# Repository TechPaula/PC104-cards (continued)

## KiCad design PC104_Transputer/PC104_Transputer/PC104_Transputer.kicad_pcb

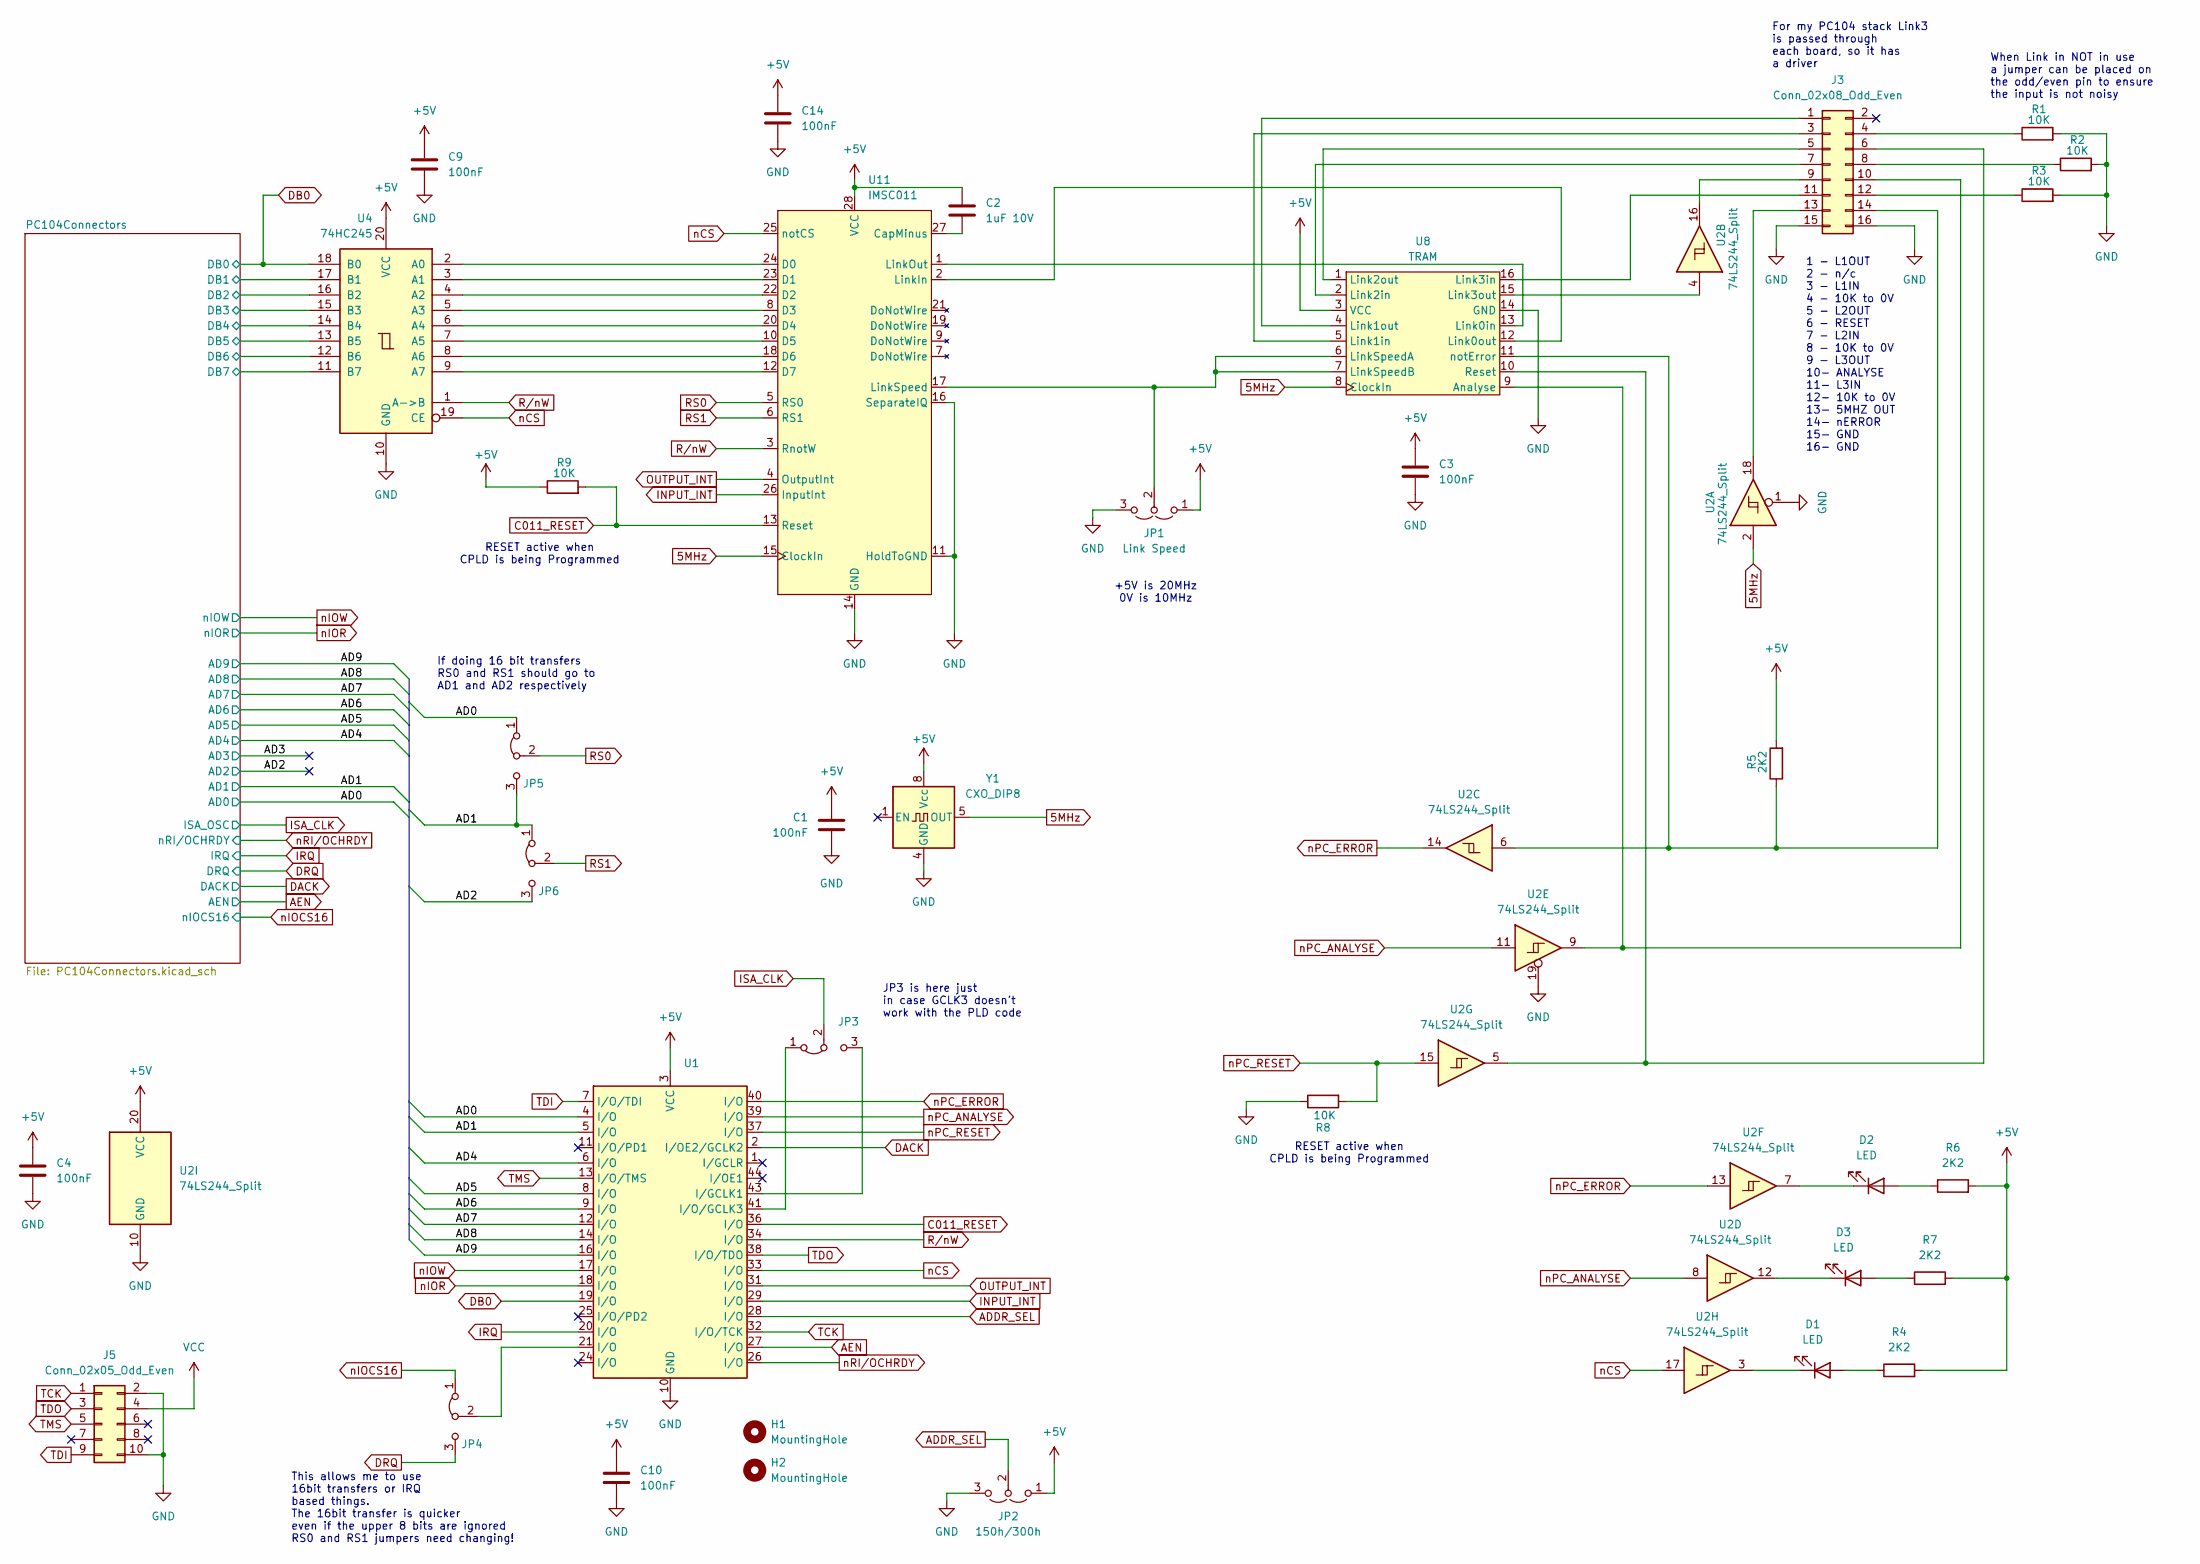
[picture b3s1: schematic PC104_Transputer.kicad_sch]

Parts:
C1, C3, C4, C9, C10, C14: 100nF; C_0805_2012Metric
C2: 1uF 10V; C_0805_2012Metric
D1, D2, D3: LED; LED_0603_1608Metric
H1, H2: MountingHole; MountingHole_2.5mm
J3: Conn_02x08_Odd_Even; PinHeader_2x08_P2.54mm_Horizontal
J5: Conn_02x05_Odd_Even; PinHeader_2x05_P2.54mm_Vertical
JP1: Link Speed; PinHeader_1x03_P2.54mm_Vertical
JP2: 150h/300h; PinHeader_1x03_P2.54mm_Vertical
JP3, JP4, JP5, JP6: Jumper_3_Bridged12; SolderJumper-3_P1.3mm_Bridged12_RoundedPad1.0x1.5mm_NumberL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
R1, R2, R3, R8, R9: 10K; R_0402_1005Metric
R4, R6, R7: 2K2; R_0603_1608Metric
R5: 2K2; R_0402_1005Metric
U1: PLCC-44_THT-Socket
U2: 74LS244_Split; SOIC-20W_7.5x12.8mm_P1.27mm
U4: 74HC245; SOIC-20W_7.5x12.8mm_P1.27mm
U8: TRAM
U11: IMSC011; DIP-28_W15.24mm
Y1: CXO_DIP8; Oscillator_DIP-8

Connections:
5MHz: U2.2, U8.8 (ClockIn), U11.15 (ClockIn), Y1.5 (OUT)
+5V: C1.1, C2.1, C3.1, C4.1, C9.1, C10.1, C14.1, JP1.1 (A), JP2.1 (A), R4.2, R5.2, R6.2, R7.2, R9.1, U1.3 (VCC), U1.15 (VCC), U1.23 (VCC), U1.35 (VCC), U2.20 (VCC), U4.20 (VCC), U8.3 (VCC), U11.28 (VCC), Y1.8 (Vcc); also elsewhere on the board
/AD0: JP5.1 (A), U1.4 (I/O); also elsewhere on the board
/AD1: JP5.3 (B), JP6.1 (A), U1.5 (I/O); also elsewhere on the board
/AD2: JP6.3 (B); also elsewhere on the board
/AD4: U1.6 (I/O); also elsewhere on the board
/AD5: U1.8 (I/O); also elsewhere on the board
/AD6: U1.9 (I/O); also elsewhere on the board
/AD7: U1.12 (I/O); also elsewhere on the board
/AD8: U1.14 (I/O); also elsewhere on the board
/AD9: U1.16 (I/O); also elsewhere on the board
/PC104Connectors/DB1: U4.17 (B1); also elsewhere on the board
/PC104Connectors/DB2: U4.16 (B2); also elsewhere on the board
/PC104Connectors/DB3: U4.15 (B3); also elsewhere on the board
/PC104Connectors/DB4: U4.14 (B4); also elsewhere on the board
/PC104Connectors/DB5: U4.13 (B5); also elsewhere on the board
/PC104Connectors/DB6: U4.12 (B6); also elsewhere on the board
/PC104Connectors/DB7: U4.11 (B7); also elsewhere on the board
ADDR_SEL: JP2.2 (C), U1.28 (I/O)
AEN: U1.27 (I/O); also elsewhere on the board
C011_RESET: R9.2, U1.36 (I/O), U11.13 (Reset)
DACK: U1.2 (I/OE2/GCLK2); also elsewhere on the board
DB0: U1.19 (I/O), U4.18 (B0); also elsewhere on the board
DRQ: JP4.3 (B); also elsewhere on the board
GND: C1.2, C3.2, C4.2, C9.2, C10.2, C14.2, J3.15, J3.16, J5.2, J5.10, JP1.3 (B), JP2.3 (B), R1.2, R2.2, R3.2, R8.1, U1.10 (GND), U1.22 (GND), U1.30 (GND), U1.42 (GND), U2.1, U2.10 (GND), U2.19, U4.10 (GND), U8.14 (GND), U11.11 (HoldToGND), U11.14 (GND), U11.16 (SeparateIQ), Y1.4 (GND); also elsewhere on the board
INPUT_INT: U1.29 (I/O), U11.26 (InputInt)
IRQ: U1.20 (I/O); also elsewhere on the board
ISA_CLK: JP3.2 (C); also elsewhere on the board
unnamed: D1.2 (A), R4.1
unnamed: D1.1 (K), U2.3
unnamed: D2.2 (A), R6.1
unnamed: D2.1 (K), U2.7
unnamed: D3.2 (A), R7.1
unnamed: D3.1 (K), U2.12
unnamed: J3.1, U8.4 (Link1out)
unnamed: J3.3, U8.5 (Link1in)
unnamed: J3.4, R1.1
unnamed: J3.5, U8.1 (Link2out)
unnamed: J3.6, U2.5, U8.10 (Reset)
unnamed: J3.7, U8.2 (Link2in)
unnamed: J3.8, R2.1
unnamed: J3.9, U2.16
unnamed: J3.10, U2.9, U8.9 (Analyse)
unnamed: J3.11, U8.16 (Link3in)
unnamed: J3.12, R3.1
unnamed: J3.13, U2.18
unnamed: J3.14, R5.1, U2.6, U8.11 (notError)
unnamed: JP1.2 (C), U8.6 (LinkSpeedA), U8.7 (LinkSpeedB), U11.17 (LinkSpeed)
unnamed: JP3.1 (A), U1.41 (I/O/GCLK3)
unnamed: JP3.3 (B), U1.43 (I/GCLK1)
unnamed: JP4.2 (C), U1.21 (I/O)
unnamed: U2.4, U8.15 (Link3out)
unnamed: C2.2, U11.27 (CapMinus)
unnamed: U4.2 (A0), U11.24 (D0)
unnamed: U4.3 (A1), U11.23 (D1)
unnamed: U4.4 (A2), U11.22 (D2)
unnamed: U4.5 (A3), U11.8 (D3)
unnamed: U4.6 (A4), U11.20 (D4)
unnamed: U4.7 (A5), U11.10 (D5)
unnamed: U4.8 (A6), U11.18 (D6)
unnamed: U4.9 (A7), U11.12 (D7)
unnamed: U8.12 (Link0out), U11.2 (LinkIn)
unnamed: U8.13 (Link0in), U11.1 (LinkOut)
OUTPUT_INT: U1.31 (I/O), U11.4 (OutputInt)
RS0: JP5.2 (C), U11.5 (RS0)
RS1: JP6.2 (C), U11.6 (RS1)
R/nW: U1.34 (I/O), U4.1 (A->B), U11.3 (RnotW)
TCK: J5.1, U1.32 (I/O/TCK)
TDI: J5.9, U1.7 (I/O/TDI)
TDO: J5.3, U1.38 (I/O/TDO)
TMS: J5.5, U1.13 (I/O/TMS)
VCC: J5.4
nCS: U1.33 (I/O), U2.17, U4.19 (CE), U11.25 (notCS)
nIOCS16: JP4.1 (A); also elsewhere on the board
nIOR: U1.18 (I/O); also elsewhere on the board
nIOW: U1.17 (I/O); also elsewhere on the board
nPC_ANALYSE: U1.39 (I/O), U2.8, U2.11
nPC_ERROR: U1.40 (I/O), U2.13, U2.14
nPC_RESET: R8.2, U1.37 (I/O), U2.15
nRI/OCHRDY: U1.26 (I/O); also elsewhere on the board

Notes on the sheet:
When Link in NOT in use a jumper can be placed on the odd/even pin to ensure the input is not noisy
RESET active when CPLD is being Programmed
JP3 is here just in case GCLK3 doesn't work with the PLD code
For my PC104 stack Link3 is passed through each board, so it has a driver
If doing 16 bit transfers RS0 and RS1 should go to AD1 and AD2 respectively
This allows me to use 16bit transfers or IRQ based things. The 16bit transfer is quicker even if the upper 8 bits are ignored RS0 and RS1 jumpers need changing!
1 - L1OUT 2 - n/c 3 - L1IN 4 - 10K to 0V 5 - L2OUT 6 - RESET 7 - L2IN 8 - 10K to 0V 9 - L3OUT 10- ANALYSE 11- L3IN 12- 10K to 0V 13- 5MHZ OUT 14- nERROR 15- GND 16- GND
+5V is 20MHz 0V is 10MHz

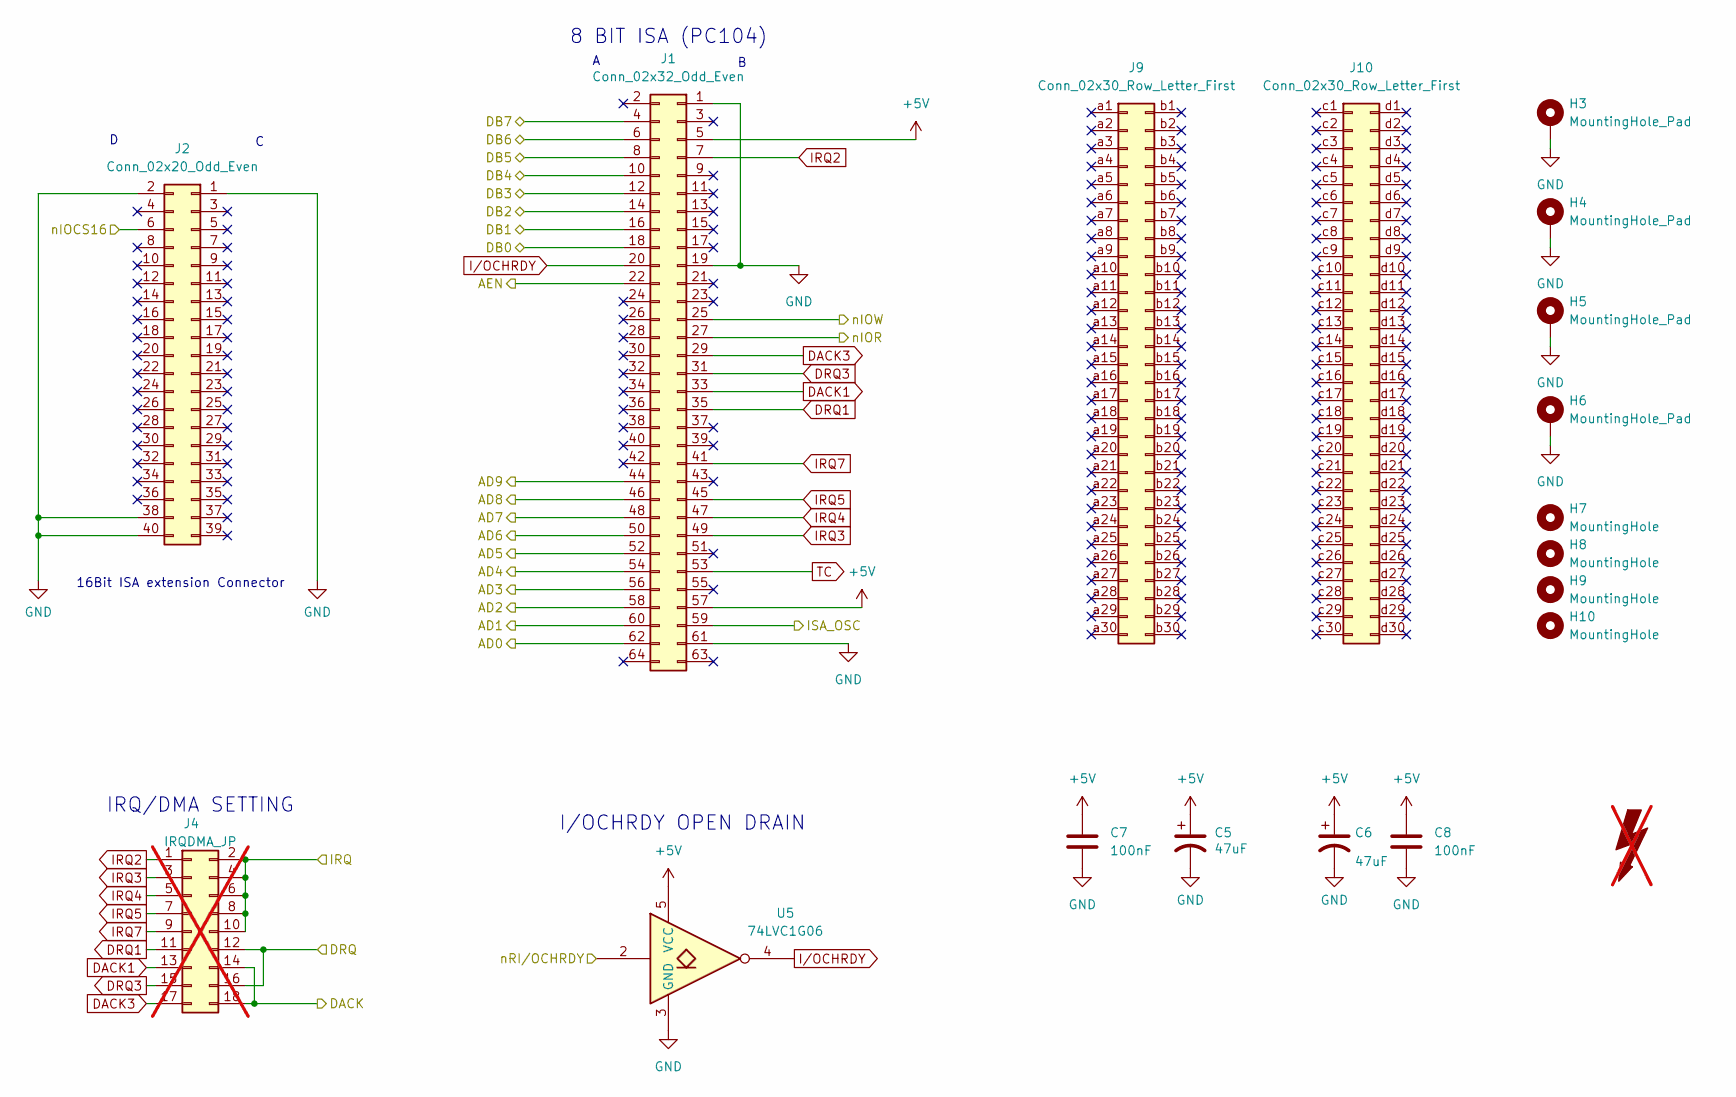
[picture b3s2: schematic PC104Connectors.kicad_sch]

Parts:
C5, C6: 47uF; C_1206_3216Metric; LCSC C96123
C7, C8: 100nF; C_0805_2012Metric
FOX1: SYM_Flash_Large; Fox_avatar_18mm; LCSC DNF; not fitted
H3, H4, H5, H6: MountingHole_Pad; MountingHole_3.2mm_M3_Pad_TopBottom; LCSC DNF
H7, H8, H9, H10: MountingHole; MountingHole_2mm; LCSC DNF
J1: Conn_02x32_Odd_Even; PinSocket_2x32_P2.54mm_Vertical; LCSC DNF
J2: Conn_02x20_Odd_Even; PinSocket_2x20_P2.54mm_Vertical; LCSC DNF
J4: IRQDMA_JP; PinHeader_2x09_P2.54mm_Vertical; LCSC DNF; not fitted
J9, J10: Conn_02x30_Row_Letter_First; PinSocket_2x30_P2.00mm_Vertical; LCSC DNF
U5: 74LVC1G06; SOT-23-5

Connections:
+5V: C5.1, C6.1, C7.1, C8.1, J1.5, J1.57, U5.5 (VCC); also elsewhere on the board
/AD0: J1.62; also elsewhere on the board
/AD1: J1.60; also elsewhere on the board
/AD2: J1.58; also elsewhere on the board
/AD3: J1.56
/AD4: J1.54; also elsewhere on the board
/AD5: J1.52; also elsewhere on the board
/AD6: J1.50; also elsewhere on the board
/AD7: J1.48; also elsewhere on the board
/AD8: J1.46; also elsewhere on the board
/AD9: J1.44; also elsewhere on the board
/PC104Connectors/DB1: J1.16; also elsewhere on the board
/PC104Connectors/DB2: J1.14; also elsewhere on the board
/PC104Connectors/DB3: J1.12; also elsewhere on the board
/PC104Connectors/DB4: J1.10; also elsewhere on the board
/PC104Connectors/DB5: J1.8; also elsewhere on the board
/PC104Connectors/DB6: J1.6; also elsewhere on the board
/PC104Connectors/DB7: J1.4; also elsewhere on the board
AEN: J1.22; also elsewhere on the board
DACK: J4.14, J4.18; also elsewhere on the board
DACK1: J1.33, J4.13
DACK3: J1.29, J4.17
DB0: J1.18; also elsewhere on the board
DRQ: J4.12, J4.16; also elsewhere on the board
DRQ1: J1.35, J4.11
DRQ3: J1.31, J4.15
GND: C5.2, C6.2, C7.2, C8.2, H3.1, H4.1, H5.1, H6.1, J1.1, J1.19, J1.61, J2.1, J2.2, J2.38, J2.40, U5.3 (GND); also elsewhere on the board
IRQ: J4.2, J4.4, J4.6, J4.8, J4.10; also elsewhere on the board
IRQ2: J1.7, J4.1
IRQ3: J1.49, J4.3
IRQ4: J1.47, J4.5
IRQ5: J1.45, J4.7
IRQ7: J1.41, J4.9
ISA_CLK: J1.59; also elsewhere on the board
I/OCHRDY: J1.20, U5.4
TC: J1.53
nIOCS16: J2.6; also elsewhere on the board
nIOR: J1.27; also elsewhere on the board
nIOW: J1.25; also elsewhere on the board
nRI/OCHRDY: U5.2; also elsewhere on the board

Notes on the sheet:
IRQ/DMA SETTING
16Bit ISA extension Connector
8 BIT ISA (PC104)
I/OCHRDY OPEN DRAIN

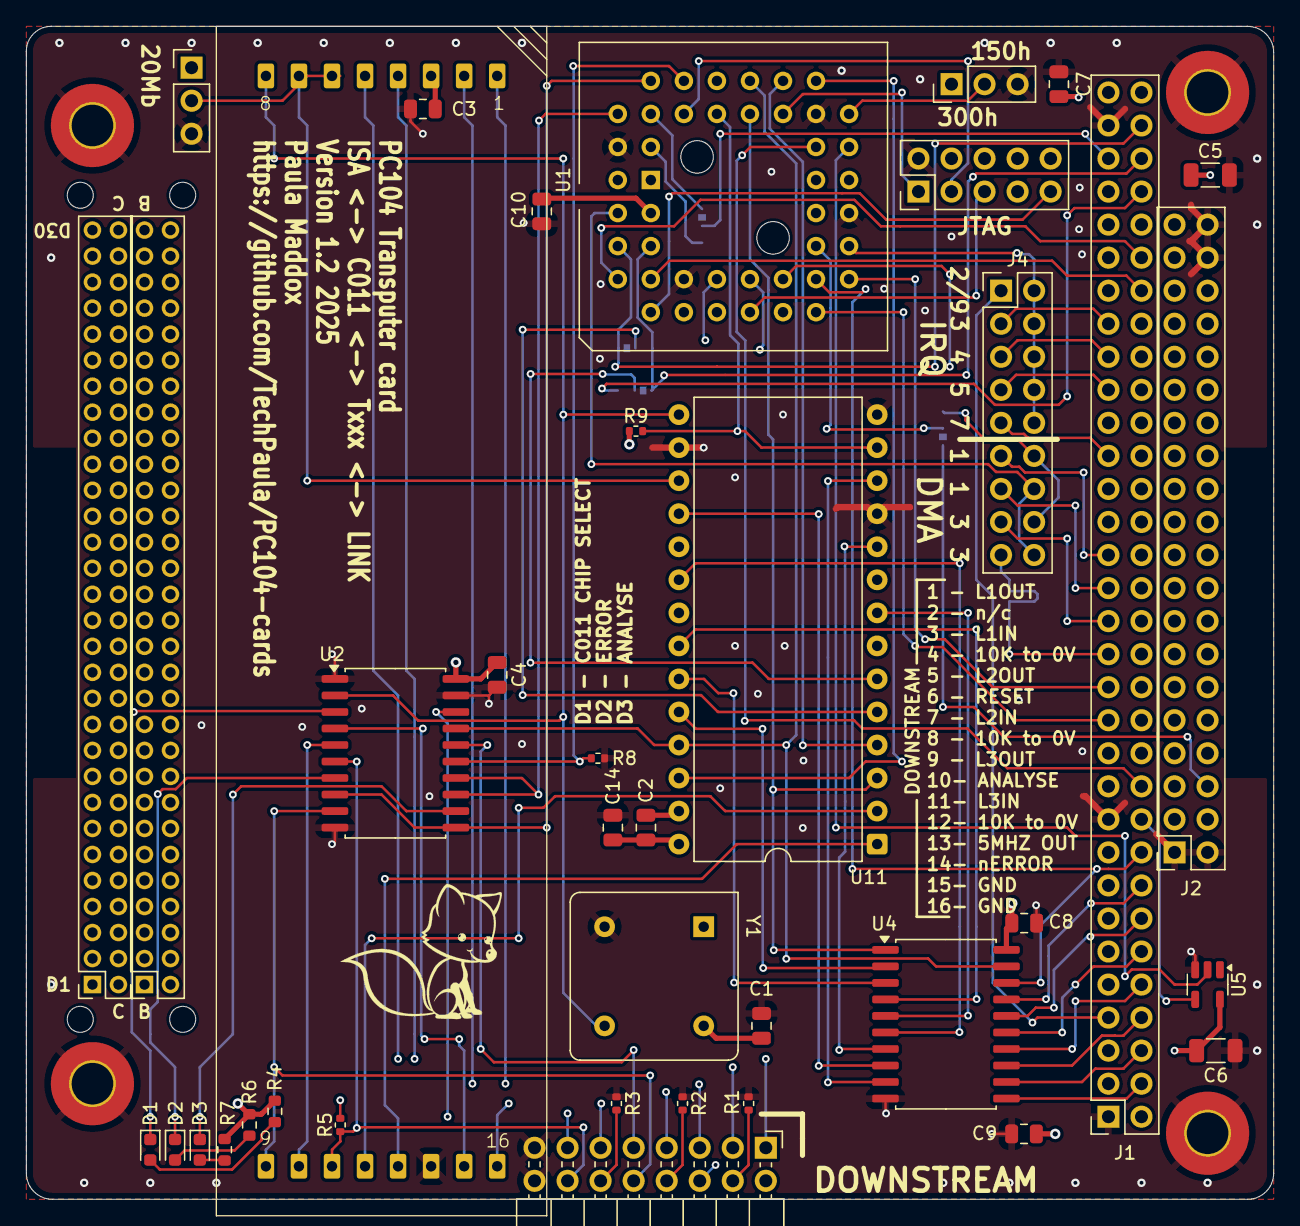
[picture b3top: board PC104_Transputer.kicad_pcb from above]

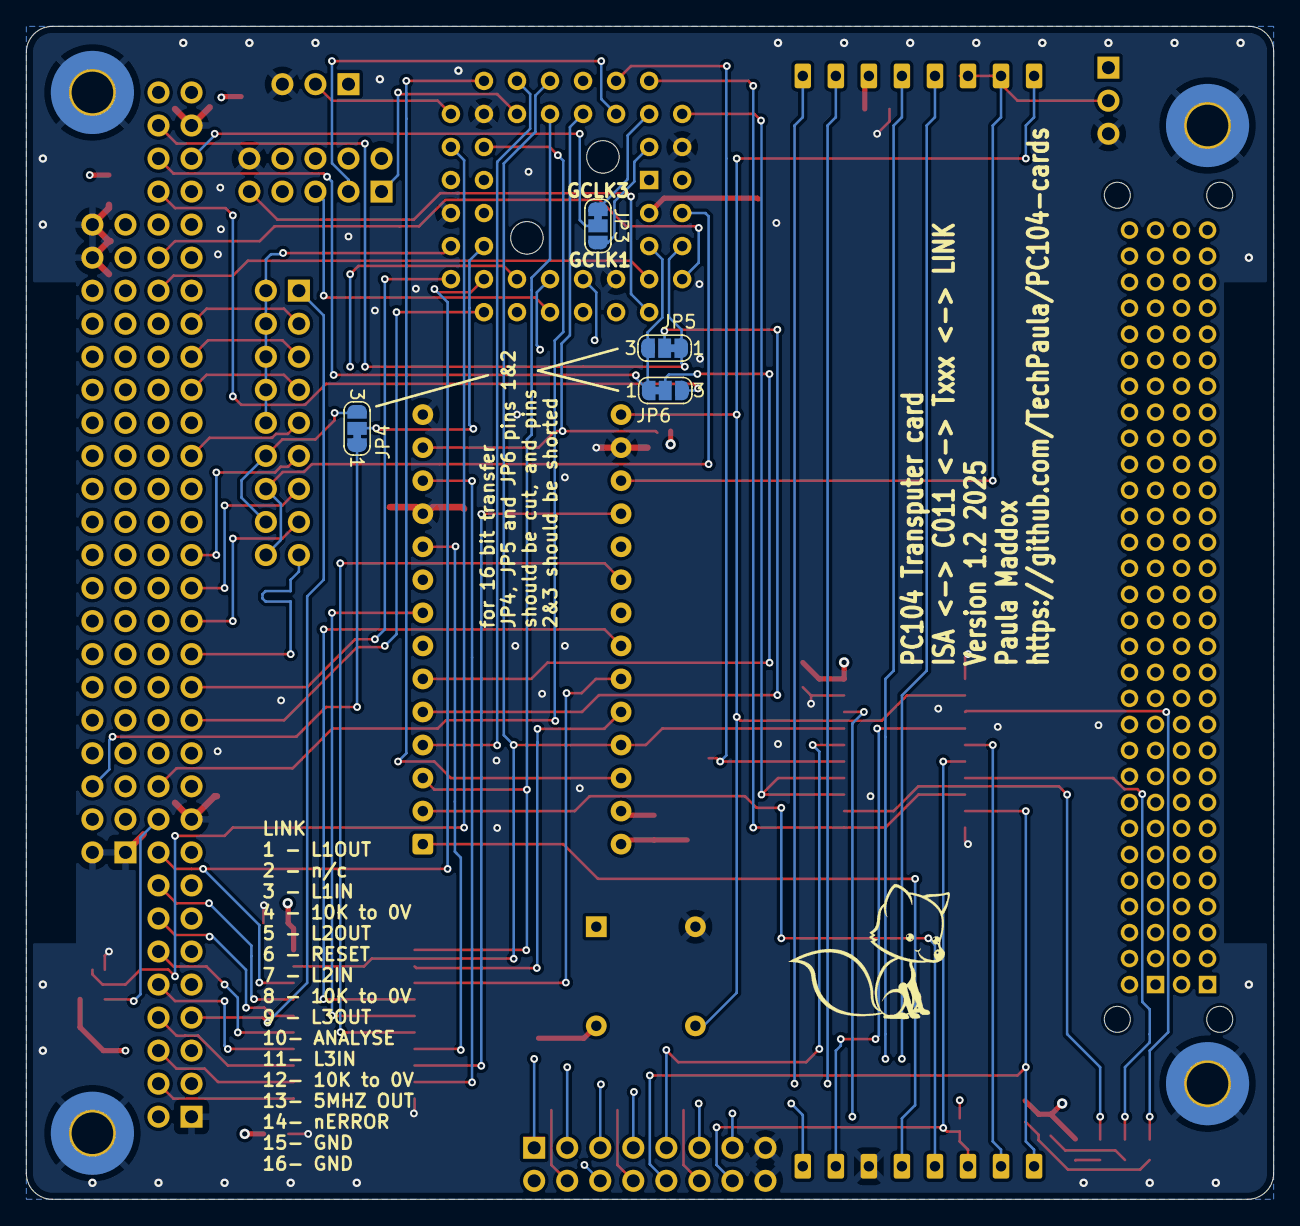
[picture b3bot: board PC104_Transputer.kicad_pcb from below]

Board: 4 copper layers, 95.9 x 90.2 mm, 55 parts (5 on the bottom side), 89 nets.

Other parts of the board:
FOX1#2: SYM_Flash_Large; Fox_avatar_18mm

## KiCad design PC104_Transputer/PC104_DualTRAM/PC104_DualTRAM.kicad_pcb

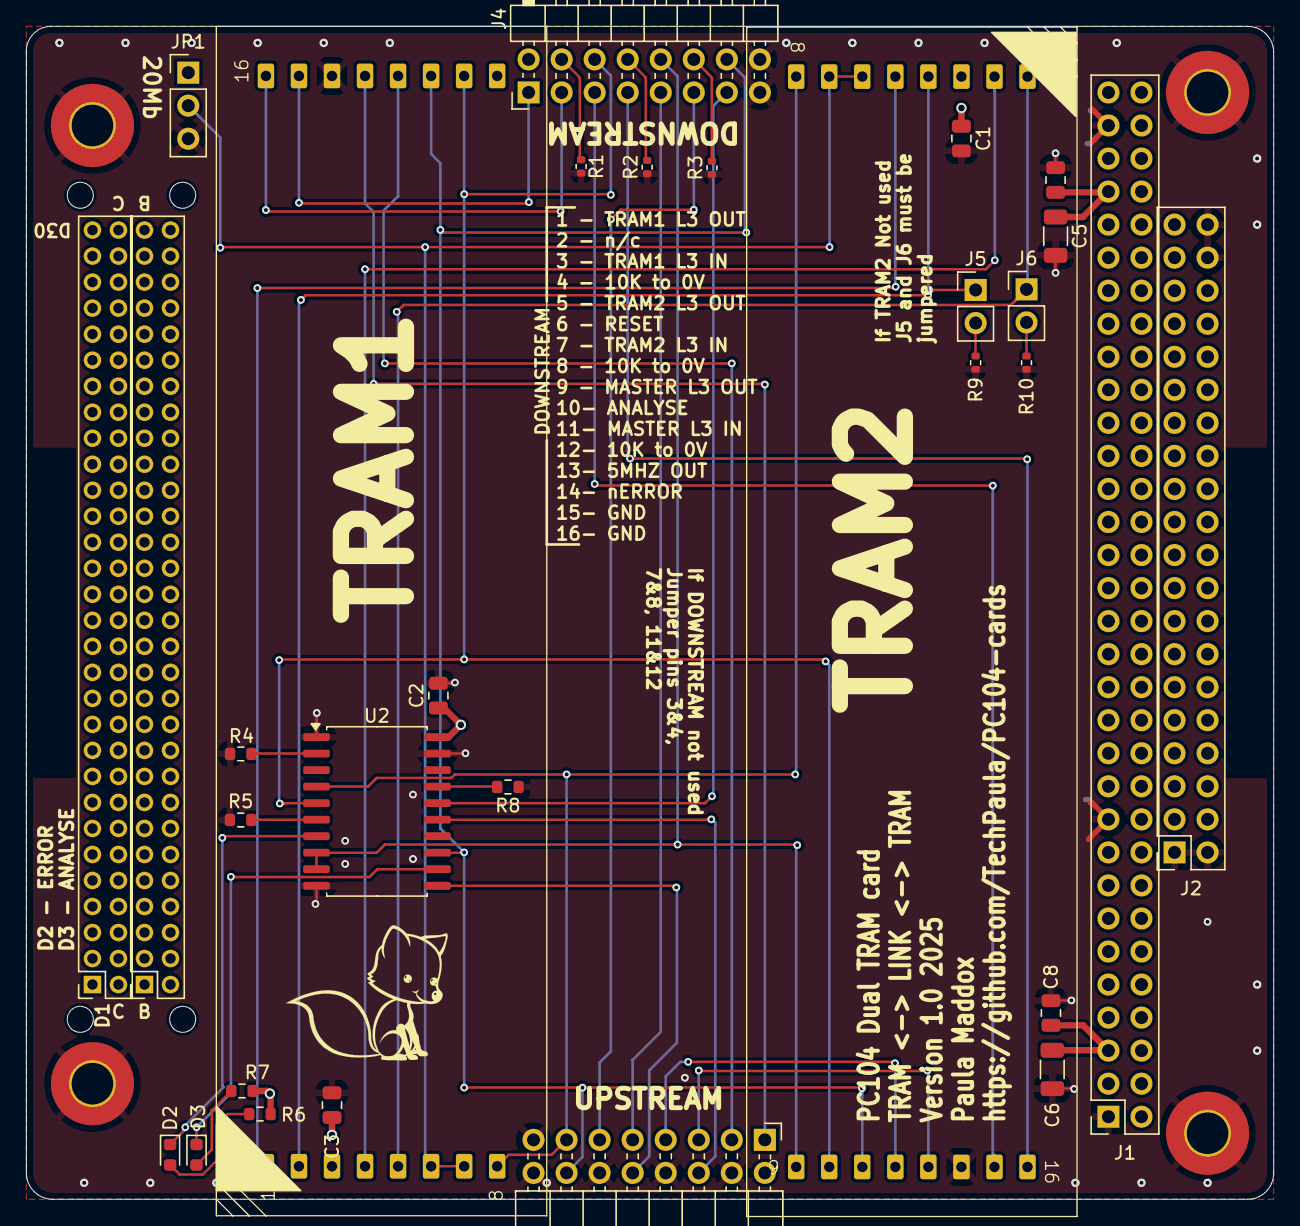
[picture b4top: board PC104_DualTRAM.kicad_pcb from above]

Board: 4 copper layers, 95.9 x 90.2 mm, 41 parts (1 on the bottom side), 36 nets.

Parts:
C1, C2, C3, C7, C8: 100nF; C_0805_2012Metric
C5, C6: 47uF; C_1206_3216Metric
D2, D3: LED; LED_0603_1608Metric
FOX1, FOX1#2: SYM_Flash_Large; Fox_avatar_18mm
H3, H4, H5, H6: MountingHole_Pad; MountingHole_3.2mm_M3_Pad_TopBottom
H7, H8, H9, H10: MountingHole; MountingHole_2mm
J1: Conn_02x32_Odd_Even; PinSocket_2x32_P2.54mm_Vertical
J2: Conn_02x20_Odd_Even; PinSocket_2x20_P2.54mm_Vertical
J3: UPSTREAM; PinHeader_2x08_P2.54mm_Horizontal
J4: DOWNSTREAM; PinHeader_2x08_P2.54mm_Horizontal
J5, J6: Conn_01x02; PinHeader_1x02_P2.54mm_Vertical
J9, J10: Conn_02x30_Row_Letter_First; PinSocket_2x30_P2.00mm_Vertical
JP1: Link Speed; PinHeader_1x03_P2.54mm_Vertical
R1, R2, R3, R9, R10: 10K; R_0402_1005Metric
R4, R5, R6, R7, R8: 2K2; R_0603_1608Metric
U1, U8: TRAM
U2: 74LS244_Split; SOIC-20W_7.5x12.8mm_P1.27mm

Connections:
5MHz: J3.13, U1.8 (ClockIn), U2.4, U8.8 (ClockIn)
+5V: C1.1, C2.1, C3.1, C5.1, C6.1, C7.1, C8.1, J1.5, J1.57, JP1.1 (A), R6.2, R7.2, U1.3 (VCC), U2.20 (VCC), U8.3 (VCC)
/5MHZ_OUT: J4.13, U2.16
/nPC_ANALYSE_IN: J3.10, U2.11
/nPC_RESET_IN: J3.6, U2.15
GND: C1.2, C2.2, C3.2, C5.2, C6.2, C7.2, C8.2, H3.1, H4.1, H5.1, H6.1, J1.1, J1.19, J1.61, J2.1, J2.2, J2.38, J2.40, J3.4, J3.8, J3.12, J3.15, J3.16, J4.15, J4.16, JP1.3 (B), R1.2, R2.2, R3.2, R4.1, R5.1, R8.1, R9.1, R10.1, U1.14 (GND), U2.1, U2.10 (GND), U2.19, U8.14 (GND)
LINK_SPEED: JP1.2 (C), U1.6 (LinkSpeedA), U1.7 (LinkSpeedB), U8.6 (LinkSpeedA), U8.7 (LinkSpeedB)
M2S_LINK1: J3.1, U8.13 (Link0in)
M2S_LINK2: J3.5, U1.13 (Link0in)
M2S_LINK3: J3.9, J4.9
unnamed: D2.2 (A), R6.1
unnamed: D2.1 (K), U2.7
unnamed: D3.2 (A), R7.1
unnamed: D3.1 (K), U2.12
unnamed: J4.4, R1.1
unnamed: J4.8, R2.1
unnamed: J4.12, R3.1
unnamed: J5.2, R9.2
unnamed: J6.2, R10.2
unnamed: R4.2, U2.2
unnamed: R5.2, U2.6
unnamed: R8.2, U2.17
S2M_LINK1: J3.3, U8.12 (Link0out)
S2M_LINK2: J3.7, U1.12 (Link0out)
S2M_LINK3: J3.11, J4.11
U1_IN_LINK3: J4.7, U1.16 (Link3in)
U1_OUT_LINK3: J4.5, U1.15 (Link3out)
U8_IN_LINK3: J4.3, U8.16 (Link3in)
U8_OUT_LINK3: J4.1, U8.15 (Link3out)
U18_LINK12: J5.1, U1.4 (Link1out), U8.2 (Link2in)
U18_LINK21: J6.1, U1.1 (Link2out), U8.5 (Link1in)
U81_LINK12: U1.2 (Link2in), U8.4 (Link1out)
U81_LINK21: U1.5 (Link1in), U8.1 (Link2out)
nPC_ANALYSE: J4.10, U1.9 (Analyse), U2.8, U2.9
nPC_ERROR: J3.14, J4.14, U1.11 (notError), U2.13, U8.11 (notError)
nPC_RESET: J4.6, U1.10 (Reset), U2.5, U8.10 (Reset)

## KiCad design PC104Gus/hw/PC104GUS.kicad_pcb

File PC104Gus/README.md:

# PC104GUS

This is just a PC104plus board for the picogus.
All credit for this remains with the original picogus project and not me, I just rerouted the board to fit my PC104+ computer.

The PCI connector is not connected and is not needed, it is there so that should I get any PCI cards in the future I can use them on my system

Audio demo is here - https://files.mastodon.social/media_attachments/files/114/795/636/375/670/314/original/4dec041206cb1098.mp4

## Update
2025-07-04 - Board assembled and fully working without any mod wires!
2025-06-21 - Board routed but NOT yet built/tested.

## License

The hardware portions of this repository (hw/ directory) are licensed under the CERN OHL version 2, permissive.

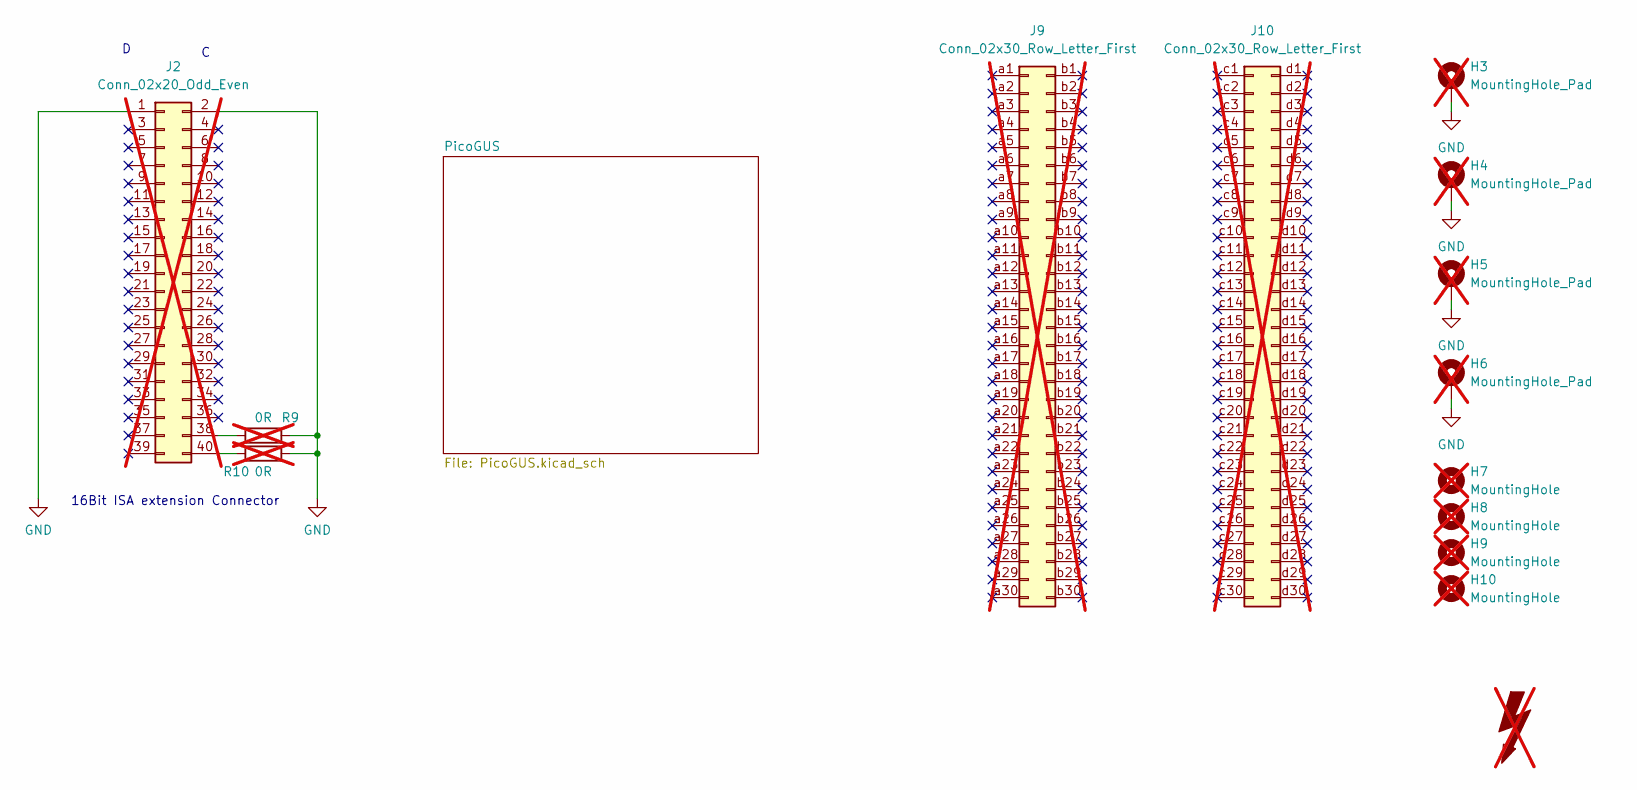
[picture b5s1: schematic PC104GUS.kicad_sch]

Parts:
FOX1: SYM_Flash_Large; Fox_avatar_18mm; LCSC DNF; not fitted
H3, H4, H5, H6: MountingHole_Pad; MountingHole_3.2mm_M3_Pad_TopBottom; LCSC DNF; not fitted
H7, H8, H9, H10: MountingHole; MountingHole_2mm; LCSC DNF; not fitted
J2: Conn_02x20_Odd_Even; PinSocket_2x20_P2.54mm_Vertical; LCSC DNF; not fitted
J9, J10: Conn_02x30_Row_Letter_First; PinSocket_2x30_P2.00mm_Vertical; LCSC DNF; not fitted
R9, R10: 0R; R_0603_1608Metric; LCSC DNF; not fitted

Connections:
GND: H3.1, H4.1, H5.1, H6.1, J2.1, J2.2, R9.2, R10.1; also elsewhere on the board
unnamed: J2.38, R9.1
unnamed: J2.40, R10.2

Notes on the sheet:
16Bit ISA extension Connector
